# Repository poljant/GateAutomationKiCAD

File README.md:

# GateAutomationKiCAD
Elektronika do GateAutomation

Wersja beta.
Moduł sterowania dwuskrzydłową bramą z oddzielną furtką.
Zasilanie siłowników 12 do 24VDC.
Możliwość zasilania zamka furtki innym napięciem np 12-24VAC.
Jeżeli chcemy zasilić siłowniki wyższym napięciem to należy wymienić U3 na taki, który bedzie przetważał te napięcie na 5VDC 0.8A.
Sterowanie za pomocą pilota 433MHz, wifi 2.4GHz i (lub) modułu HC11 (433MHz).
Gniazda J2 i J3 do podłączenia odbiornika RF 433MHz.
Gniazdo J5 do podłączenia nadajnika RF 433MHz.
Gniazdo J7 do podłączenia układu komunikacji na 433MHz (HC11 lub HC12).
Siłowniki i zamek furtki zabezpieczone są prze zwarciem.
Program do tego układu jest w trakcie tworzenia i testów na repozytorum GateAutomation.
Dalsze informacje będą uzupełniane w trakcie tworzenia i testów.

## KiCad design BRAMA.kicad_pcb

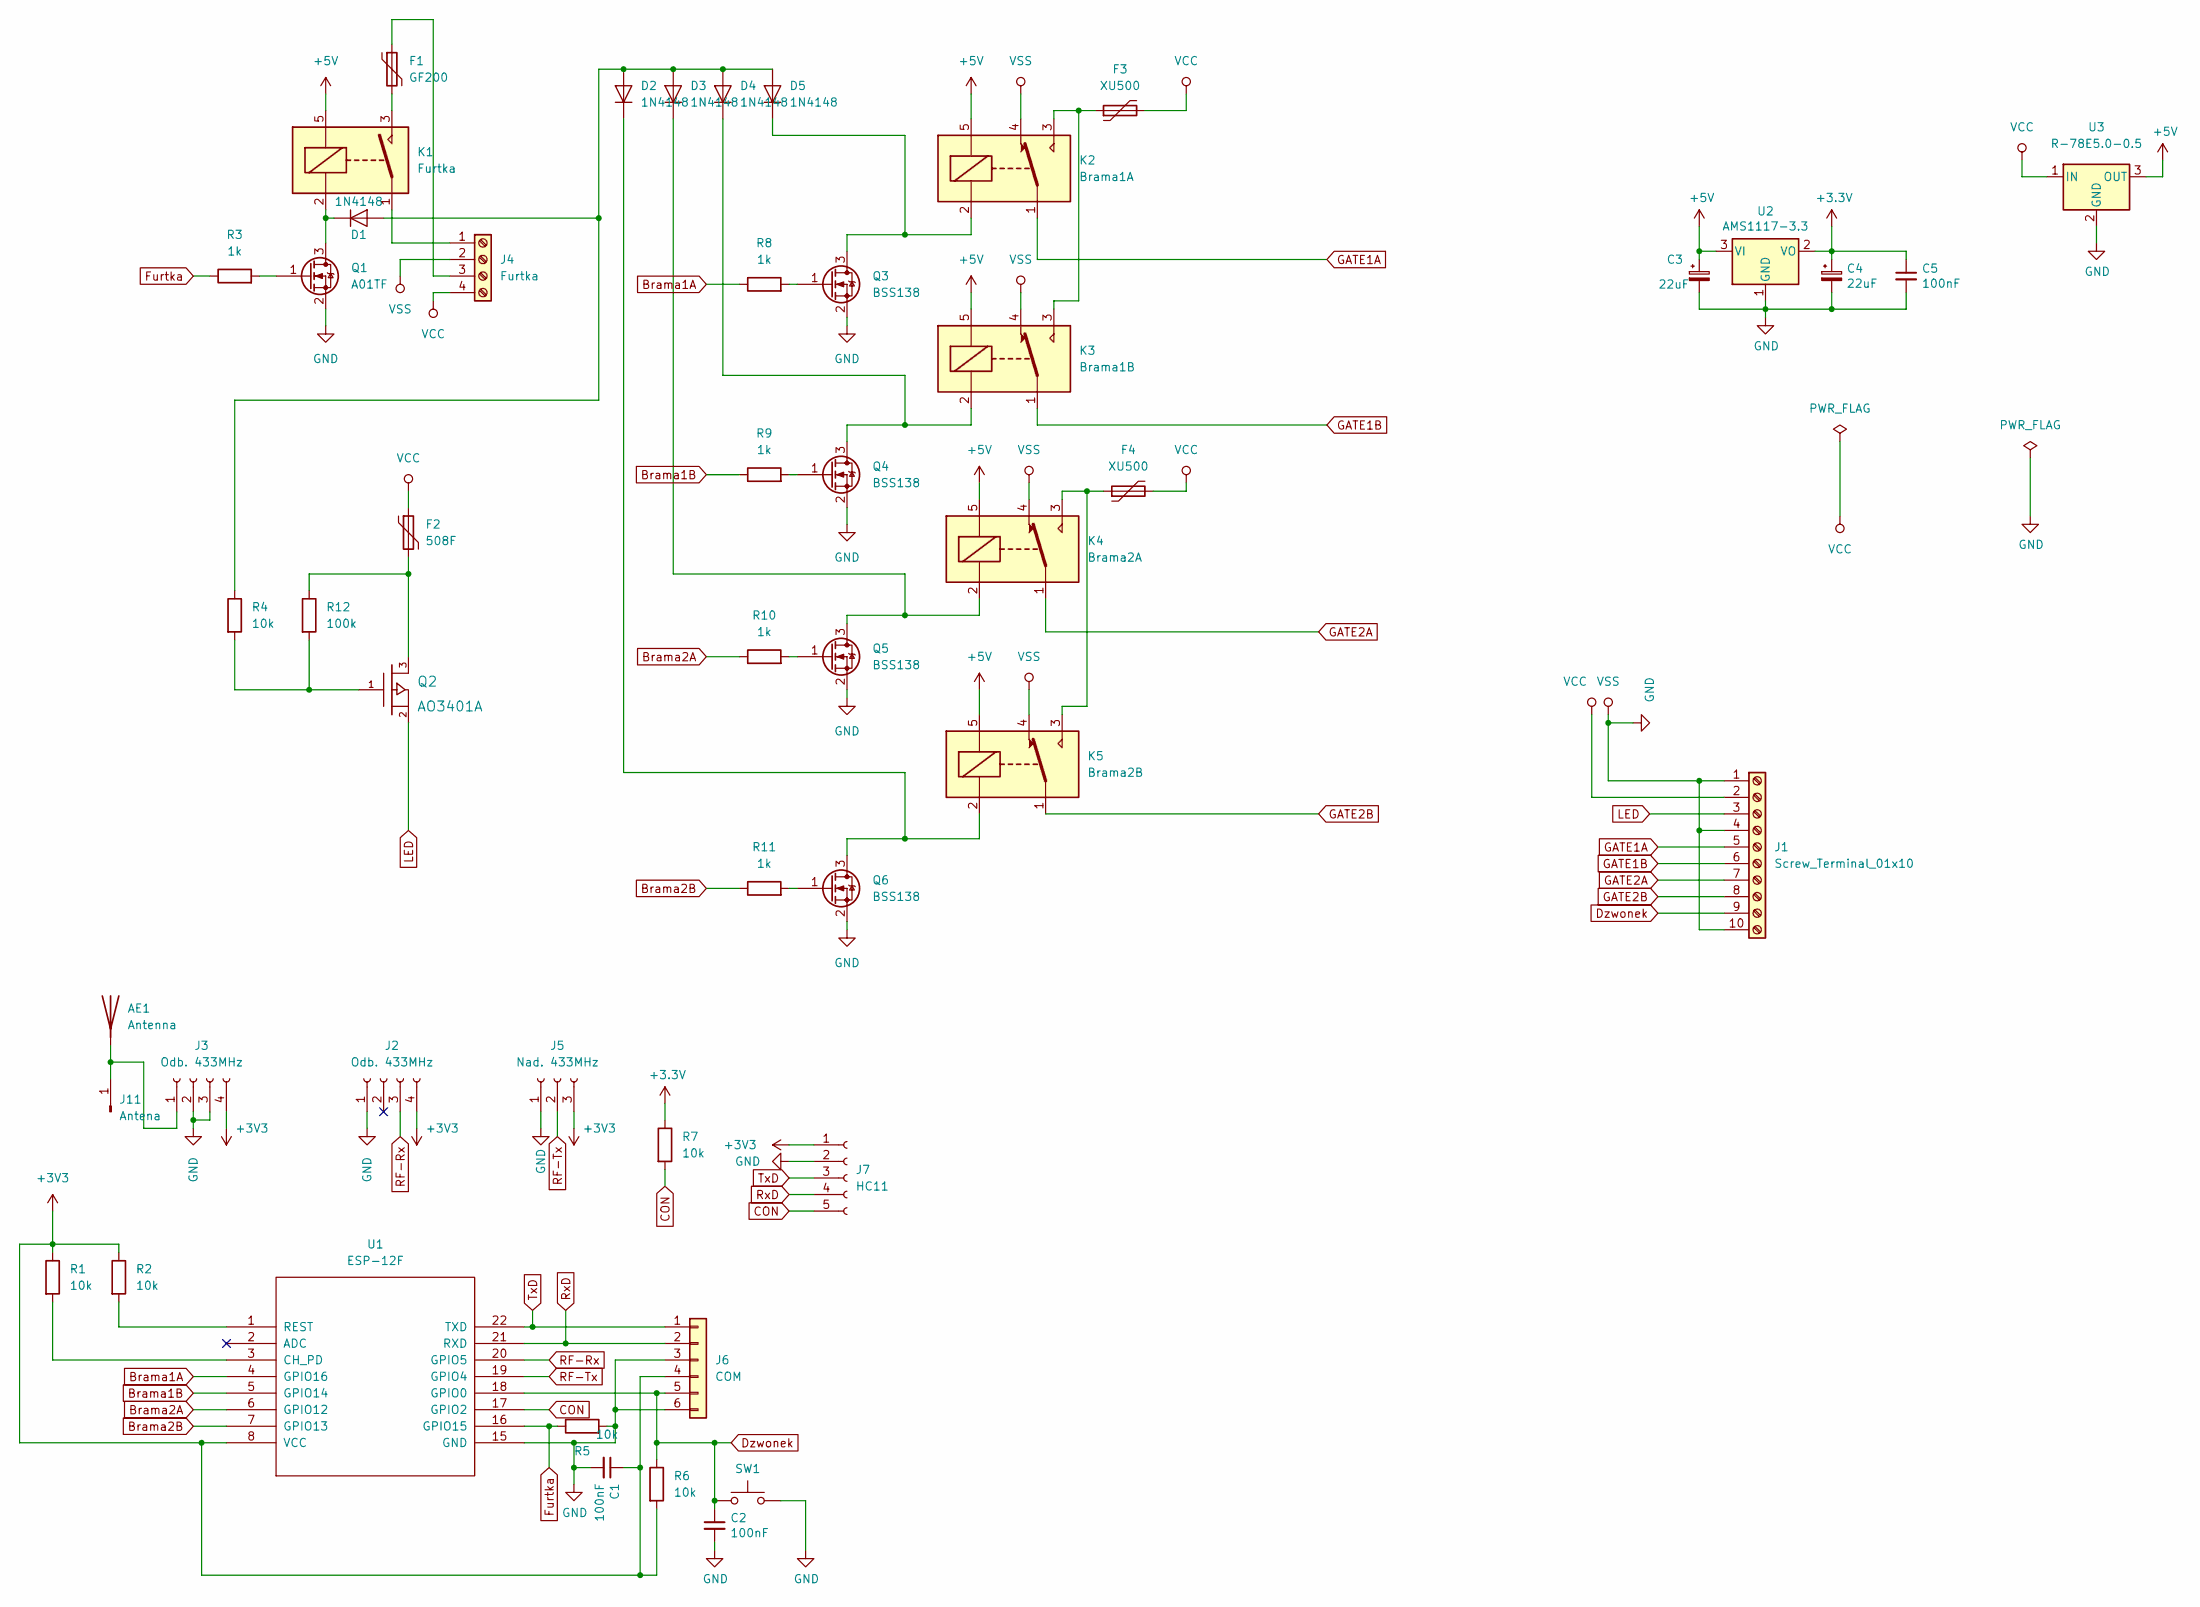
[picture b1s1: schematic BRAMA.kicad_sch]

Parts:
AE1: Antenna
C1, C2, C5: 100nF; C_1206_3216Metric_Pad1.42x1.75mm_HandSolder
C3, C4: 22uF; CP_Elec_5x4.5
D1, D2, D3, D4, D5: 1N4148; D_SOD-123
F1: GF200; R_Axial_DIN0204_L3.6mm_D1.6mm_P5.08mm_Horizontal
F2: 508F; R_1812_4532Metric_Pad1.30x3.40mm_HandSolder
F3, F4: XU500; R_Axial_DIN0207_L6.3mm_D2.5mm_P10.16mm_Horizontal
J1: Screw_Terminal_01x10; TerminalBlock_Phoenix_MKDS-1,5-10-5.08_1x10_P5.08mm_Horizon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
J2, J3: Odb. 433MHz; PinSocket_1x04_P2.54mm_Vertical
J4: Furtka; TerminalBlock_bornier-4_P5.08mm
J5: Nad. 433MHz; PinSocket_1x03_P2.54mm_Vertical
J6: COM; PinSocket_1x06_P2.54mm_Vertical
J7: HC11; PinSocket_1x05_P2.54mm_Vertical
J11: Antena; PinHeader_1x01_P2.54mm_Vertical
K1: Furtka; Relay_SPDT_SANYOU_SRA_Series_Form_C
K2: Brama1A; Relay_SPDT_SANYOU_SRD_Series_Form_C
K3: Brama1B; Relay_SPDT_SANYOU_SRD_Series_Form_C
K4: Brama2A; Relay_SPDT_SANYOU_SRD_Series_Form_C
K5: Brama2B; Relay_SPDT_SANYOU_SRD_Series_Form_C
Q1: A01TF; SOT-23
Q2: AO3401A; SOT-23_Handsoldering
Q3, Q4, Q5, Q6: BSS138; SOT-23
R1, R2, R4, R5, R6, R7: 10k; R_0805_2012Metric_Pad1.15x1.40mm_HandSolder
R3, R8, R9, R10, R11: 1k; R_0805_2012Metric_Pad1.15x1.40mm_HandSolder
R12: 100k; R_0805_2012Metric_Pad1.15x1.40mm_HandSolder
SW1: SW_Push; SW_SPST_EVPBF
U1: ESP-12F; ESP-12E
U2: AMS1117-3.3; SOT-223-3_TabPin2
U3: R-78E5.0-0.5; Converter_DCDC_RECOM_R-78E-0.5_THT

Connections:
+5V: C3.1, K1.5, K2.5, K3.5, K4.5, K5.5, U2.3 (VI), U3.3 (OUT)
Brama1A: R8.1, U1.4 (GPIO16)
Brama1B: R9.1, U1.5 (GPIO14)
Brama2A: R10.1, U1.6 (GPIO12)
Brama2B: R11.1, U1.7 (GPIO13)
CON: J7.5, R7.2, U1.17 (GPIO2)
Dzwonek: C2.1, J1.9, J6.5, R6.1, SW1.1, U1.18 (GPIO0)
Furtka: R3.1, R5.1, U1.16 (GPIO15)
GATE1A: J1.5, K2.1
GATE1B: J1.6, K3.1
GATE2A: J1.7, K4.1
GATE2B: J1.8, K5.1
GND: C1.2, C2.2, C3.2, C4.2, C5.2, J1.1, J1.4, J1.10, J2.1, J3.2, J3.3, J4.2, J5.1, J6.3, J6.6, J7.2, K2.4, K3.4, K4.4, K5.4, Q1.2 (S), Q3.2 (S), Q4.2 (S), Q5.2 (S), Q6.2 (S), R5.2, SW1.2, U1.15 (GND), U2.1 (GND), U3.2 (GND); also elsewhere on the board
LED: J1.3, Q2.2 (S)
unnamed: AE1.1, J3.1, J11.1
unnamed: D1.1 (K), K1.2, Q1.3 (D)
unnamed: D1.2 (A), D2.2 (A), D3.2 (A), D4.2 (A), D5.2 (A), R4.1
unnamed: D2.1 (K), K5.2, Q6.3 (D)
unnamed: D3.1 (K), K4.2, Q5.3 (D)
unnamed: D4.1 (K), K3.2, Q4.3 (D)
unnamed: D5.1 (K), K2.2, Q3.3 (D)
unnamed: F1.1, J4.3
unnamed: F1.2, K1.3
unnamed: F2.2, Q2.3 (D), R12.1
unnamed: F3.1, K2.3, K3.3
unnamed: F4.1, K4.3, K5.3
unnamed: J4.1, K1.1
unnamed: Q1.1 (G), R3.2
unnamed: Q2.1 (G), R4.2, R12.2
unnamed: Q3.1 (G), R8.2
unnamed: Q4.1 (G), R9.2
unnamed: Q5.1 (G), R10.2
unnamed: Q6.1 (G), R11.2
unnamed: R1.2, U1.3 (CH_PD)
unnamed: R2.2, U1.1 (REST)
RF-Rx: J2.3, U1.20 (GPIO5)
RF-Tx: J5.2, U1.19 (GPIO4)
RxD: J6.2, J7.4, U1.21 (RXD)
TxD: J6.1, J7.3, U1.22 (TXD)
VCC: F2.1, F3.2, F4.2, J1.2, J4.4, U3.1 (IN)

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
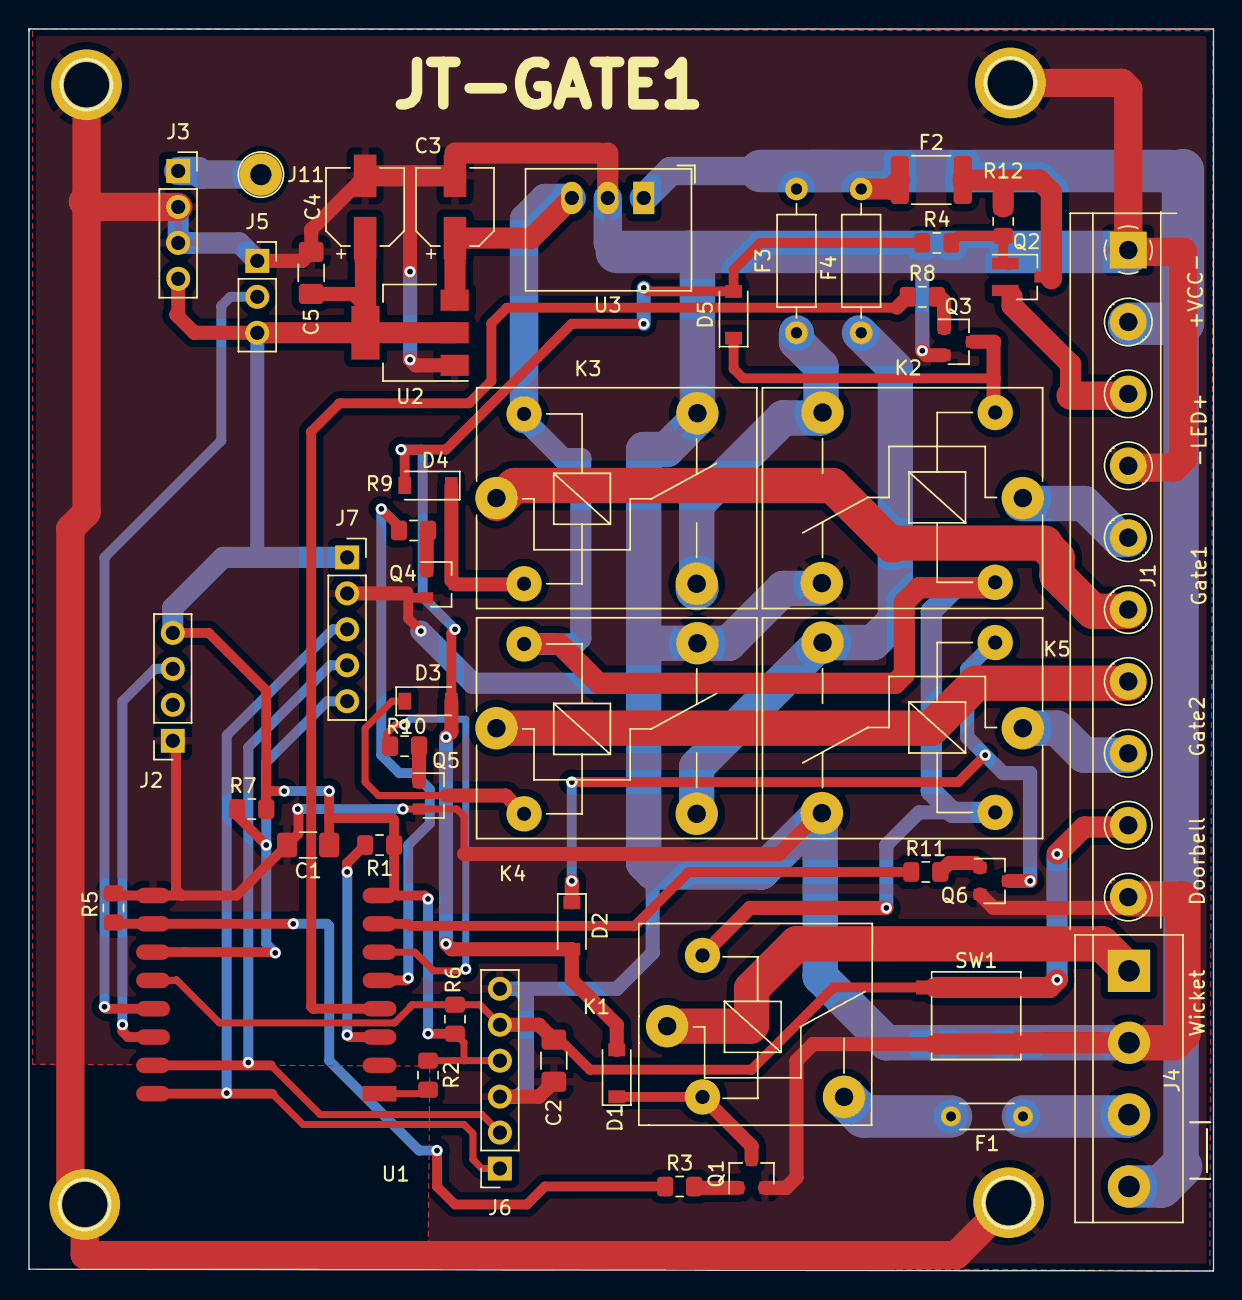
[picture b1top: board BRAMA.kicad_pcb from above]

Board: 2 copper layers, 83.7 x 87.8 mm, 53 parts (0 on the bottom side), 41 nets.

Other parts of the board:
pad_3mm, pad_3mm#2, pad_3mm#3, pad_3mm#4: VAL**; pad_3mm

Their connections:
GND: pad_3mm.1, pad_3mm#2.1, pad_3mm#3.1, pad_3mm#4.1; also elsewhere on the board

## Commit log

2022-05-07 dodanie plikow
2022-05-07 dodano informacje w pluku README
